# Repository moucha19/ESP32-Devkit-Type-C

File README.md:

ESP32 Devkit Type C
===================

## 2022 Update ([*@moucha19*](https://github.com/moucha19))

First of all, I would like to thank the original author for his work. I wanted to make this DevKit as soon as I saw it. However, there were some issues that I thought needed fixing. For example, some components were unavailable or not up-to-date. Here is a full list of my updates that all together make revision **EC**:

* CH340G was changed to CH340C to remove the need for external crystal. I also noticed that it's powered from VBUS, which according to datasheet means that the data lines will run on 5 volts. This might not kill ESP32 right away, but from what I read, it isn't good.
* I replaced MP2359 with MP2259, because the former is not recommended for new designs. JLCPCB still has MP2359s, but I wanted this update to last a while.
* USB-C connector was changed to TYPE-C-31-M-12, which I already had home. Push buttons were also changed for the same reason, but in my opinion they look good and are also pretty common.
* Inductor was replaced with currently available part 
* Some components were moved around to avoid unnecesary DRC errors
* I made pads around ESP32 larger for easier manual soldering, since I don't intend to use SMT assembly service. However, I still generated files for those who do. Use [SMT BOM](jlcpcb/bom_jlc_smt.csv) in the order to get only recommended parts (no USB-C, buttons or headers).
* Project was upgraded to Kicad 6.0

# Description

This PCB is a USB Type C enabled ESP32 development board. It is pin-compatible
with the ESP32 Devkit C but sports a slightly decreased width to fit on a
standard breadboard.  

# Features

* USB Type C
* pin-compatible with ESP32 Devkit
* fits on standard breadboard
* onboard antenna
* jumper to short USB protection diode

Furthermore this board is optimized for JLCPCB assembly, a Chinese SMT PCB
assembly service. All components on this board, except the USB Type C connector,
the push buttons and the pin headers can be assembled by them for around ~$8
including PCB manufacturing and components.

# Assembly

There is an
[interactive HTML BOM](https://htmlpreview.github.io/?https://github.com/moucha19/ESP32-Devkit-Type-C/blob/master/docs/ibom.html)
to help you assemble the board.

Assuming you are using JLCPCB SMT assembly you will need to populate just the
following parts by hand:

| Reference  | Description            | LCSC                                                                                                                  |
|------------|------------------------|-----------------------------------------------------------------------------------------------------------------------|
| J1         | USB Type C connector   | [C165948](https://www.lcsc.com/product-detail/USB-Type-C_Korean-Hroparts-Elec-TYPE-C-31-M-12_C165948.html)    |
| SW1, SW2   | RESET/BOOT push button | [C589212](https://lcsc.com/product-detail/Tactile-Switches_RI-SHENG-ST-1188_C589212.html)    |
| J2, J3     | Pin headers            | [C2337](https://lcsc.com/product-detail/Pin-Header-Female-Header_BOOMELE-Boom-Precision-Elec-2-54mm-1x40P_C2337.html) |

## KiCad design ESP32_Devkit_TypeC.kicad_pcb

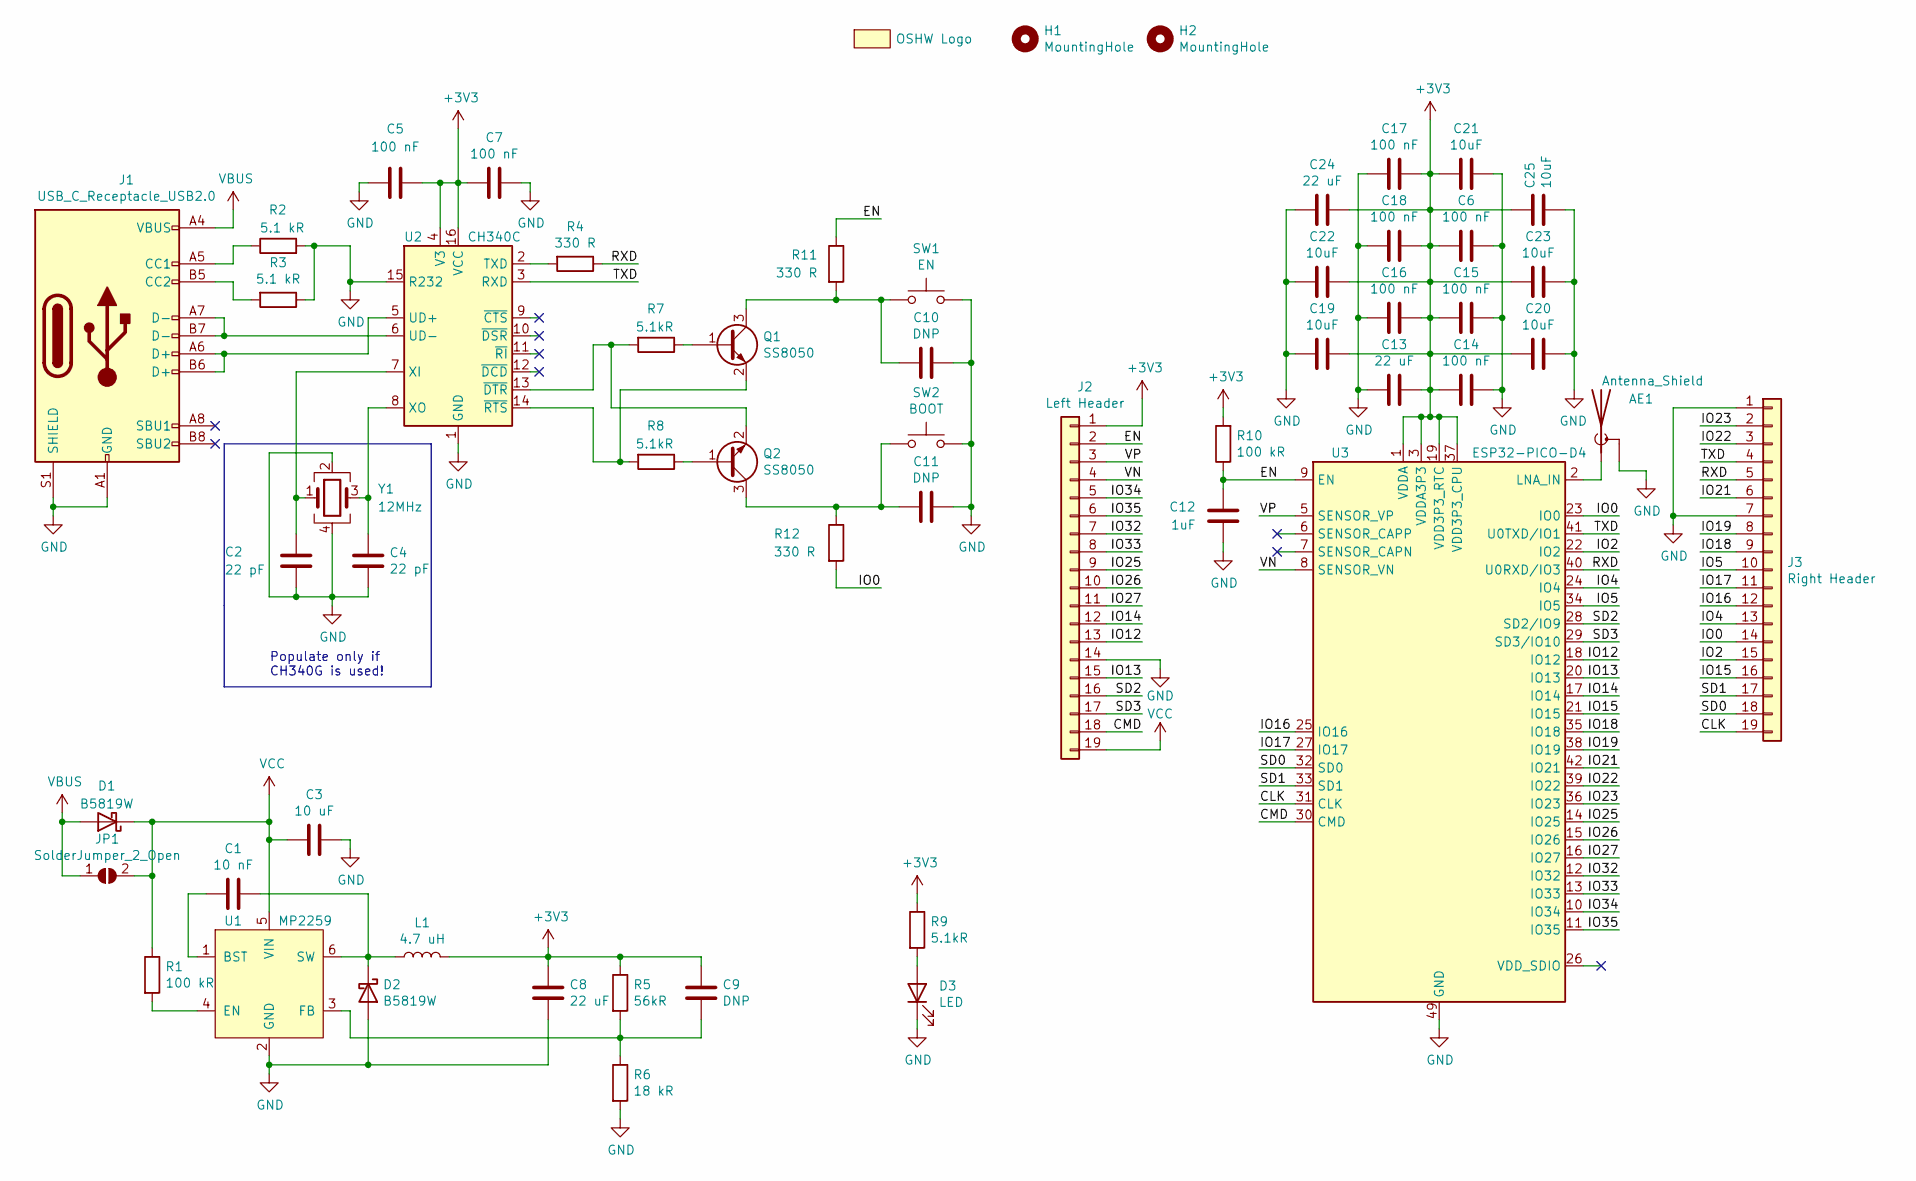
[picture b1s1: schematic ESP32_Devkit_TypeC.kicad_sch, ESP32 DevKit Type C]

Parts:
AE1: Antenna_Shield; Antenna_IFA_2.4GHz_meandered
C1: 10 nF; C_0402_1005Metric; LCSC C15195
C2, C4: 22 pF; C_0402_1005Metric; LCSC C1555
C3: 10 uF; C_0805_2012Metric; LCSC C15850
C5, C6, C7, C14, C15, C16, C17, C18: 100 nF; C_0402_1005Metric; LCSC C1525
C8, C13, C24: 22 uF; C_0603_1608Metric; LCSC C59461
C9, C10, C11: DNP; C_0402_1005Metric
C12: 1uF; C_0402_1005Metric; LCSC C52923
C19, C20, C21, C22: 10uF; C_0402_1005Metric; LCSC C15525
C23, C25: 10uF; C_0603_1608Metric; LCSC C19702
D1, D2: B5819W; D_SOD-123; LCSC C8598
D3: LED; LED_0603_1608Metric_Castellated; LCSC C2286
H1, H2: MountingHole; ToolingHole_JLCSMT
I2: OSHW Logo; OSHW_icon_3.3x3
J1: USB_C_Receptacle_USB2.0; USB_C_Receptacle_HRO_TYPE-C-31-M-12; LCSC C165948
J2: Left Header; PinHeader_1x19_P2.54mm_Vertical
J3: Right Header; PinHeader_1x19_P2.54mm_Vertical
JP1: SolderJumper_2_Open; SolderJumper-2_P1.3mm_Open_Pad1.0x1.5mm
L1: 4.7 uH; L_1210_3225Metric; LCSC C90319
Q1, Q2: SS8050; SOT-23; LCSC C2150
R1, R10: 100 kR; R_0402_1005Metric; LCSC C25741
R2, R3: 5.1 kR; R_0402_1005Metric; LCSC C25905
R4, R11, R12: 330 R; R_0402_1005Metric; LCSC C25104
R5: 56kR; R_0402_1005Metric; LCSC C25796
R6: 18 kR; R_0402_1005Metric; LCSC C25762
R7, R8, R9: 5.1kR; R_0402_1005Metric; LCSC C25905
SW1: EN; SW_Push_1P1T_Vertical_3x4mm; LCSC C589212
SW2: BOOT; SW_Push_1P1T_Vertical_3x4mm; LCSC C589212
U1: MP2259; SOT-23-6; LCSC C82266
U2: CH340C; SOIC-16_3.9x9.9mm_P1.27mm; LCSC C84681
U3: ESP32-PICO-D4; ESP32-Pico-D4-Thermal; LCSC C193707
Y1: 12MHz; Crystal_SMD_3225-4Pin_3.2x2.5mm; LCSC C9002

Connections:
+3V3: C5.2, C6.2, C7.2, C8.1, C9.1, C13.1, C14.2, C15.2, C16.1, C17.1, C18.1, C19.1, C20.2, C21.2, C22.1, C23.2, C24.1, C25.1, J2.1, L1.2, R5.1, R9.1, R10.2, U2.4 (V3), U2.16 (VCC), U3.1 (VDDA), U3.3 (VDDA3P3), U3.4 (VDDA3P3), U3.19 (VDD3P3_RTC), U3.37 (VDD3P3_CPU), U3.43 (VDDA), U3.46 (VDDA)
/CLK: J3.19, U3.31 (CLK)
/CMD: J2.18, U3.30 (CMD)
/EN: C12.1, J2.2, R10.1, R11.1, U3.9 (EN)
/IO0: J3.14, R12.2, U3.23 (IO0)
/IO2: J3.15, U3.22 (IO2)
/IO4: J3.13, U3.24 (IO4)
/IO5: J3.10, U3.34 (IO5)
/IO12: J2.13, U3.18 (IO12)
/IO13: J2.15, U3.20 (IO13)
/IO14: J2.12, U3.17 (IO14)
/IO15: J3.16, U3.21 (IO15)
/IO16: J3.12, U3.25 (IO16)
/IO17: J3.11, U3.27 (IO17)
/IO18: J3.9, U3.35 (IO18)
/IO19: J3.8, U3.38 (IO19)
/IO21: J3.6, U3.42 (IO21)
/IO22: J3.3, U3.39 (IO22)
/IO23: J3.2, U3.36 (IO23)
/IO25: J2.9, U3.14 (IO25)
/IO26: J2.10, U3.15 (IO26)
/IO27: J2.11, U3.16 (IO27)
/IO32: J2.7, U3.12 (IO32)
/IO33: J2.8, U3.13 (IO33)
/IO34: J2.5, U3.10 (IO34)
/IO35: J2.6, U3.11 (IO35)
/RXD: J3.5, R4.1, U3.40 (U0RXD/IO3)
/SD0: J3.18, U3.32 (SD0)
/SD1: J3.17, U3.33 (SD1)
/SD2: J2.16, U3.28 (SD2/IO9)
/SD3: J2.17, U3.29 (SD3/IO10)
/TXD: J3.4, U2.3 (RXD), U3.41 (U0TXD/IO1)
/VN: J2.4, U3.8 (SENSOR_VN)
/VP: J2.3, U3.5 (SENSOR_VP)
GND: AE1.2 (Shield), C2.2, C3.1, C4.2, C5.1, C6.1, C7.1, C8.2, C10.1, C11.1, C12.2, C13.2, C14.1, C15.1, C16.2, C17.2, C18.2, C19.2, C20.1, C21.1, C22.2, C23.1, C24.2, C25.2, D2.2 (A), D3.1 (K), J1.A1 (GND), J1.A12 (GND), J1.B1 (GND), J1.B12 (GND), J1.S1 (SHIELD), J2.14, J3.1, J3.7, R2.2, R3.1, R6.2, SW1.2, SW2.2, U1.2 (GND), U2.1 (GND), U2.15 (R232), U3.49 (GND), Y1.2, Y1.4
unnamed: AE1.1 (A), U3.2 (LNA_IN)
unnamed: C1.1, D2.1 (K), L1.1, U1.6 (SW)
unnamed: C1.2, U1.1 (BST)
unnamed: C2.1, U2.7 (XI), Y1.1
unnamed: C4.1, U2.8 (XO), Y1.3
unnamed: C9.2, R5.2, R6.1, U1.3 (FB)
unnamed: C10.2, Q1.3 (C), R11.2, SW1.1
unnamed: C11.2, Q2.3 (C), R12.1, SW2.1
unnamed: D3.2 (A), R9.2
unnamed: J1.A5 (CC1), R2.1
unnamed: J1.A6 (D+), J1.B6 (D+), U2.5 (UD+)
unnamed: J1.A7 (D-), J1.B7 (D-), U2.6 (UD-)
unnamed: J1.B5 (CC2), R3.2
unnamed: Q1.1 (B), R7.1
unnamed: Q1.2 (E), R8.2, U2.14 (~RTS)
unnamed: Q2.1 (B), R8.1
unnamed: Q2.2 (E), R7.2, U2.13 (~DTR)
unnamed: R1.2, U1.4 (EN)
unnamed: R4.2, U2.2 (TXD)
VBUS: D1.2 (A), J1.A4 (VBUS), J1.A9 (VBUS), J1.B4 (VBUS), J1.B9 (VBUS), JP1.1 (A)
VCC: C3.2, D1.1 (K), J2.19, JP1.2 (B), R1.1, U1.5 (VIN)

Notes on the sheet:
Populate only if CH340G is used!

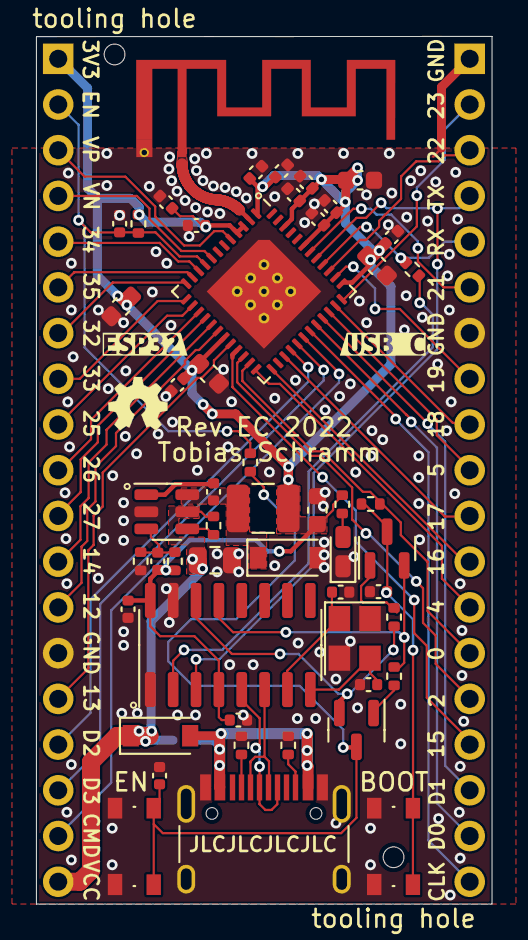
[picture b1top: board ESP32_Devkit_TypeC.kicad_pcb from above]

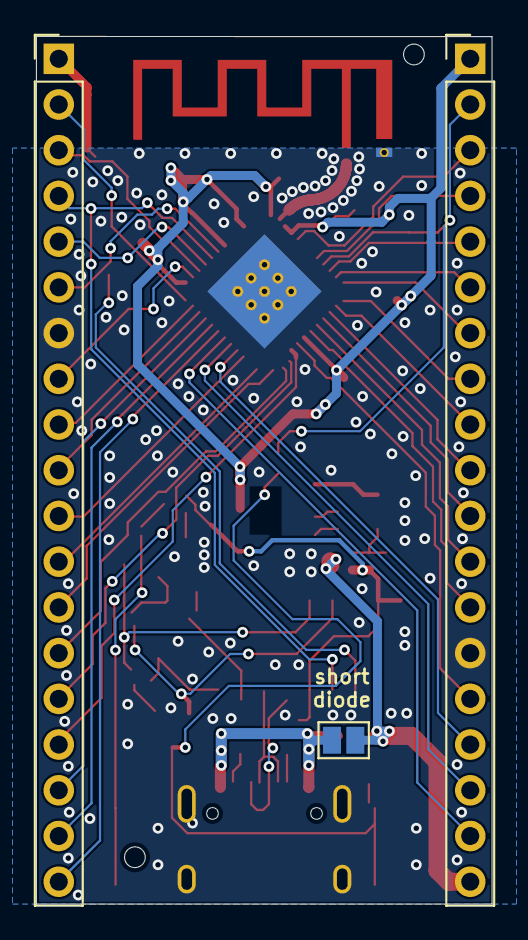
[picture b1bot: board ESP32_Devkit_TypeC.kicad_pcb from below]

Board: 2 copper layers, 25.3 x 48.2 mm, 59 parts (3 on the bottom side), 56 nets.

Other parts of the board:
kibuzzard-62337F52: G***; kibuzzard-62337F52
kibuzzard-62337F79: G***; kibuzzard-62337F79

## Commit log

2022-03-12 Migrated project to Kicad 6.0, removed unnecessary files
2022-03-13 Updated DC-DC convertor, fixed CH340G Vout
    I changed switching regulator to MP2259, because MP2359 is not recommended for new designs and is therefore more futureproof.
    Resistor values was also changed to lower the voltage from 3.5V to 3.33V.
    I also changed USB-C type to TYPE-C-31-M-12, because I have it :) It also seems to be more popular and I saw many compatible clones on Aliexpress for example.
    CH340G was set to operate with 5V signals, which isn't good for ESP, so I changed it. I also changed the part to CH340C to avoid using external crystal (which will be optional for CH340G compatibilit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
2022-03-13 Changed 4.7uF inductor part
2022-03-13 Updated footprints, reconnected CH340C
2022-03-13 Changed button type, DRC fixes
2022-03-13 updated documentation
2022-03-13 Fixed component rotation
2022-03-13 Updated readme, fixed default BOM view
2022-03-17 Rev EB serial transciever bugfix, component upgrade
2022-03-22 Rev EC
    updated ESP32 footprint based on datasheet, minor silkscreen fixes
